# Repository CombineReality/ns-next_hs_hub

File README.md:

# ns-next_hs_hub
USB 2 (High Speed) hub board for northstar-next headsets

Designed by Alex Chu for Combine Reality and EyeSeeAR

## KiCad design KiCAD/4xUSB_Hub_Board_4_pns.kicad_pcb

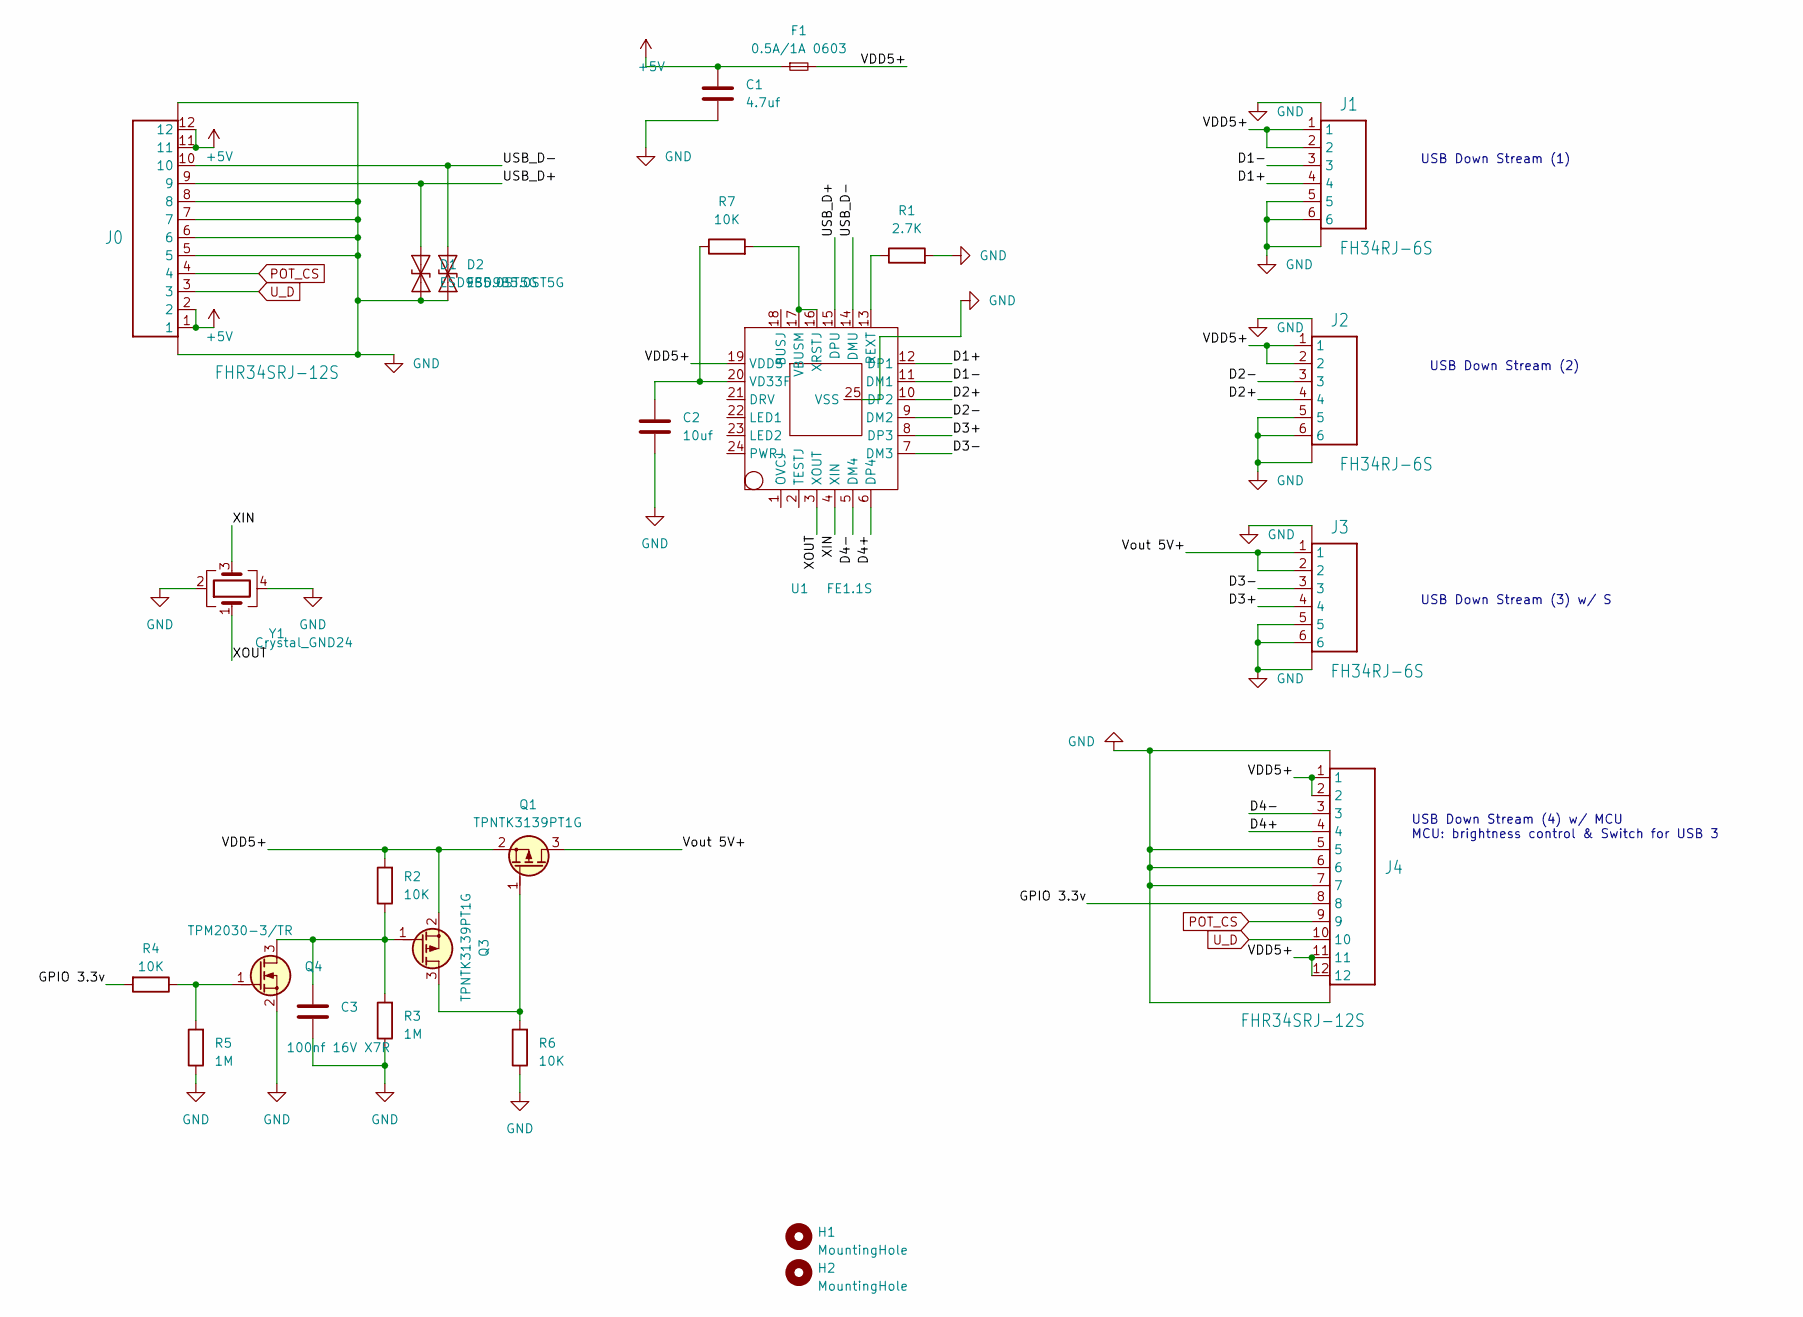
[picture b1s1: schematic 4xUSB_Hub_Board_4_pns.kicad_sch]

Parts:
C1: 4.7uf; C_0603_1608Metric
C2: 10uf; C_0603_1608Metric
C3: 100nf 16V X7R; C_0402_1005Metric
D1, D2: ESD9B5.0ST5G; D_0603_1608Metric
F1: 0.5A/1A 0603; Fuse_0603_1608Metric
H1, H2: MountingHole; MountingHole_2.1mm
J0, J4: FHR34SRJ-12S; FPC-0.5-12P
J1, J2, J3: FH34RJ-6S
Q1, Q3: TPNTK3139PT1G; SOT723
Q4: TPM2030-3/TR; SOT723
R1: 2.7K; R_0402_1005Metric
R2, R4, R6, R7: 10K; R_0402_1005Metric
R3, R5: 1M; R_0402_1005Metric
U1: FE1.1S; FE1.1S_QFN-24_narrow
Y1: Crystal_GND24; Crystal_SMD_2520-4Pin_2.5x2.0mm

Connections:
+5V: C1.1, F1.1, J0.1, J0.2, J0.11, J0.12
/D1+: J1.4, U1.12 (DP1)
/D1-: J1.3, U1.11 (DM1)
/D2+: J2.4, U1.10 (DP2)
/D2-: J2.3, U1.9 (DM2)
/D3+: J3.4, U1.8 (DP3)
/D3-: J3.3, U1.7 (DM3)
/D4+: J4.4, U1.6 (DP4)
/D4-: J4.3, U1.5 (DM4)
/GPIO 3.3v: J4.8, R4.2
/USB_D+: D1.2 (A2), J0.9, U1.15 (DPU)
/USB_D-: D2.2 (A2), J0.10, U1.14 (DMU)
/VDD5+: F1.2, J1.1, J1.2, J2.1, J2.2, J4.1, J4.2, J4.11, J4.12, Q1.2 (S), Q3.2 (S), R2.2, U1.19 (VDD5)
/Vout 5V+: J3.1, J3.2, Q1.3 (D)
/XIN: U1.4 (XIN), Y1.3
/XOUT: U1.3 (XOUT), Y1.1
GND: C1.2, C2.2, C3.2, D1.1 (A1), D2.1 (A1), J0.5, J0.6, J0.7, J0.8, J0.P$13 (G1), J0.P$14 (G2), J1.5, J1.6, J1.MH1 (G1), J1.MH2 (G2), J2.5, J2.6, J2.MH1 (G1), J2.MH2 (G2), J3.5, J3.6, J3.MH1 (G1), J3.MH2 (G2), J4.5, J4.6, J4.7, J4.P$13 (G1), J4.P$14 (G2), Q4.2 (S), R1.2, R3.1, R5.1, R6.1, U1.25 (VSS), Y1.2, Y1.4
unnamed: Q1.1 (G), Q3.3 (D), R6.2
unnamed: C3.1, Q3.1 (G), Q4.3 (D), R2.1, R3.2
unnamed: Q4.1 (G), R4.1, R5.2
unnamed: R1.1, U1.13 (REXT)
unnamed: R7.2, U1.16 (XRSTJ), U1.17 (VBUSM)
unnamed: C2.1, R7.1, U1.20 (VD33F)
POT_CS: J0.4, J4.9
U_D: J0.3, J4.10

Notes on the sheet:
USB Down Stream (3) w/ S
USB Down Stream (4) w/ MCU MCU: brightness control & Switch for USB 3
USB Down Stream (2)
USB Down Stream (1)

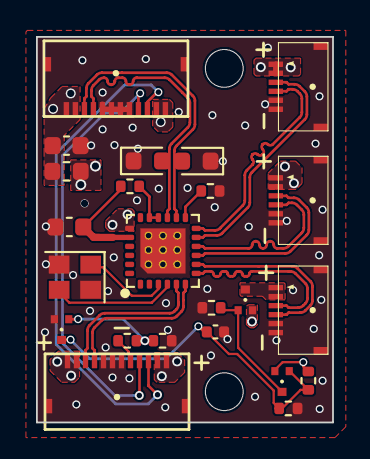
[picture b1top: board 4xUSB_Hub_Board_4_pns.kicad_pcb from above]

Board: 4 copper layers, 16.5 x 21.4 mm, 25 parts (0 on the bottom side), 25 nets.

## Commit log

2024-04-24 Update README.md
    Added credit for Alex Chu
2024-04-24 added .gitignore file for KiCad and initial source docs
2024-05-08 Added more 3D models, PDF
    Added missing 3D models, mainly to make CAD easier (connectors) and nicer. Also generated a PDF of the schematic for a quick reference without opening KiCad.
    Done with KiCad V8.
